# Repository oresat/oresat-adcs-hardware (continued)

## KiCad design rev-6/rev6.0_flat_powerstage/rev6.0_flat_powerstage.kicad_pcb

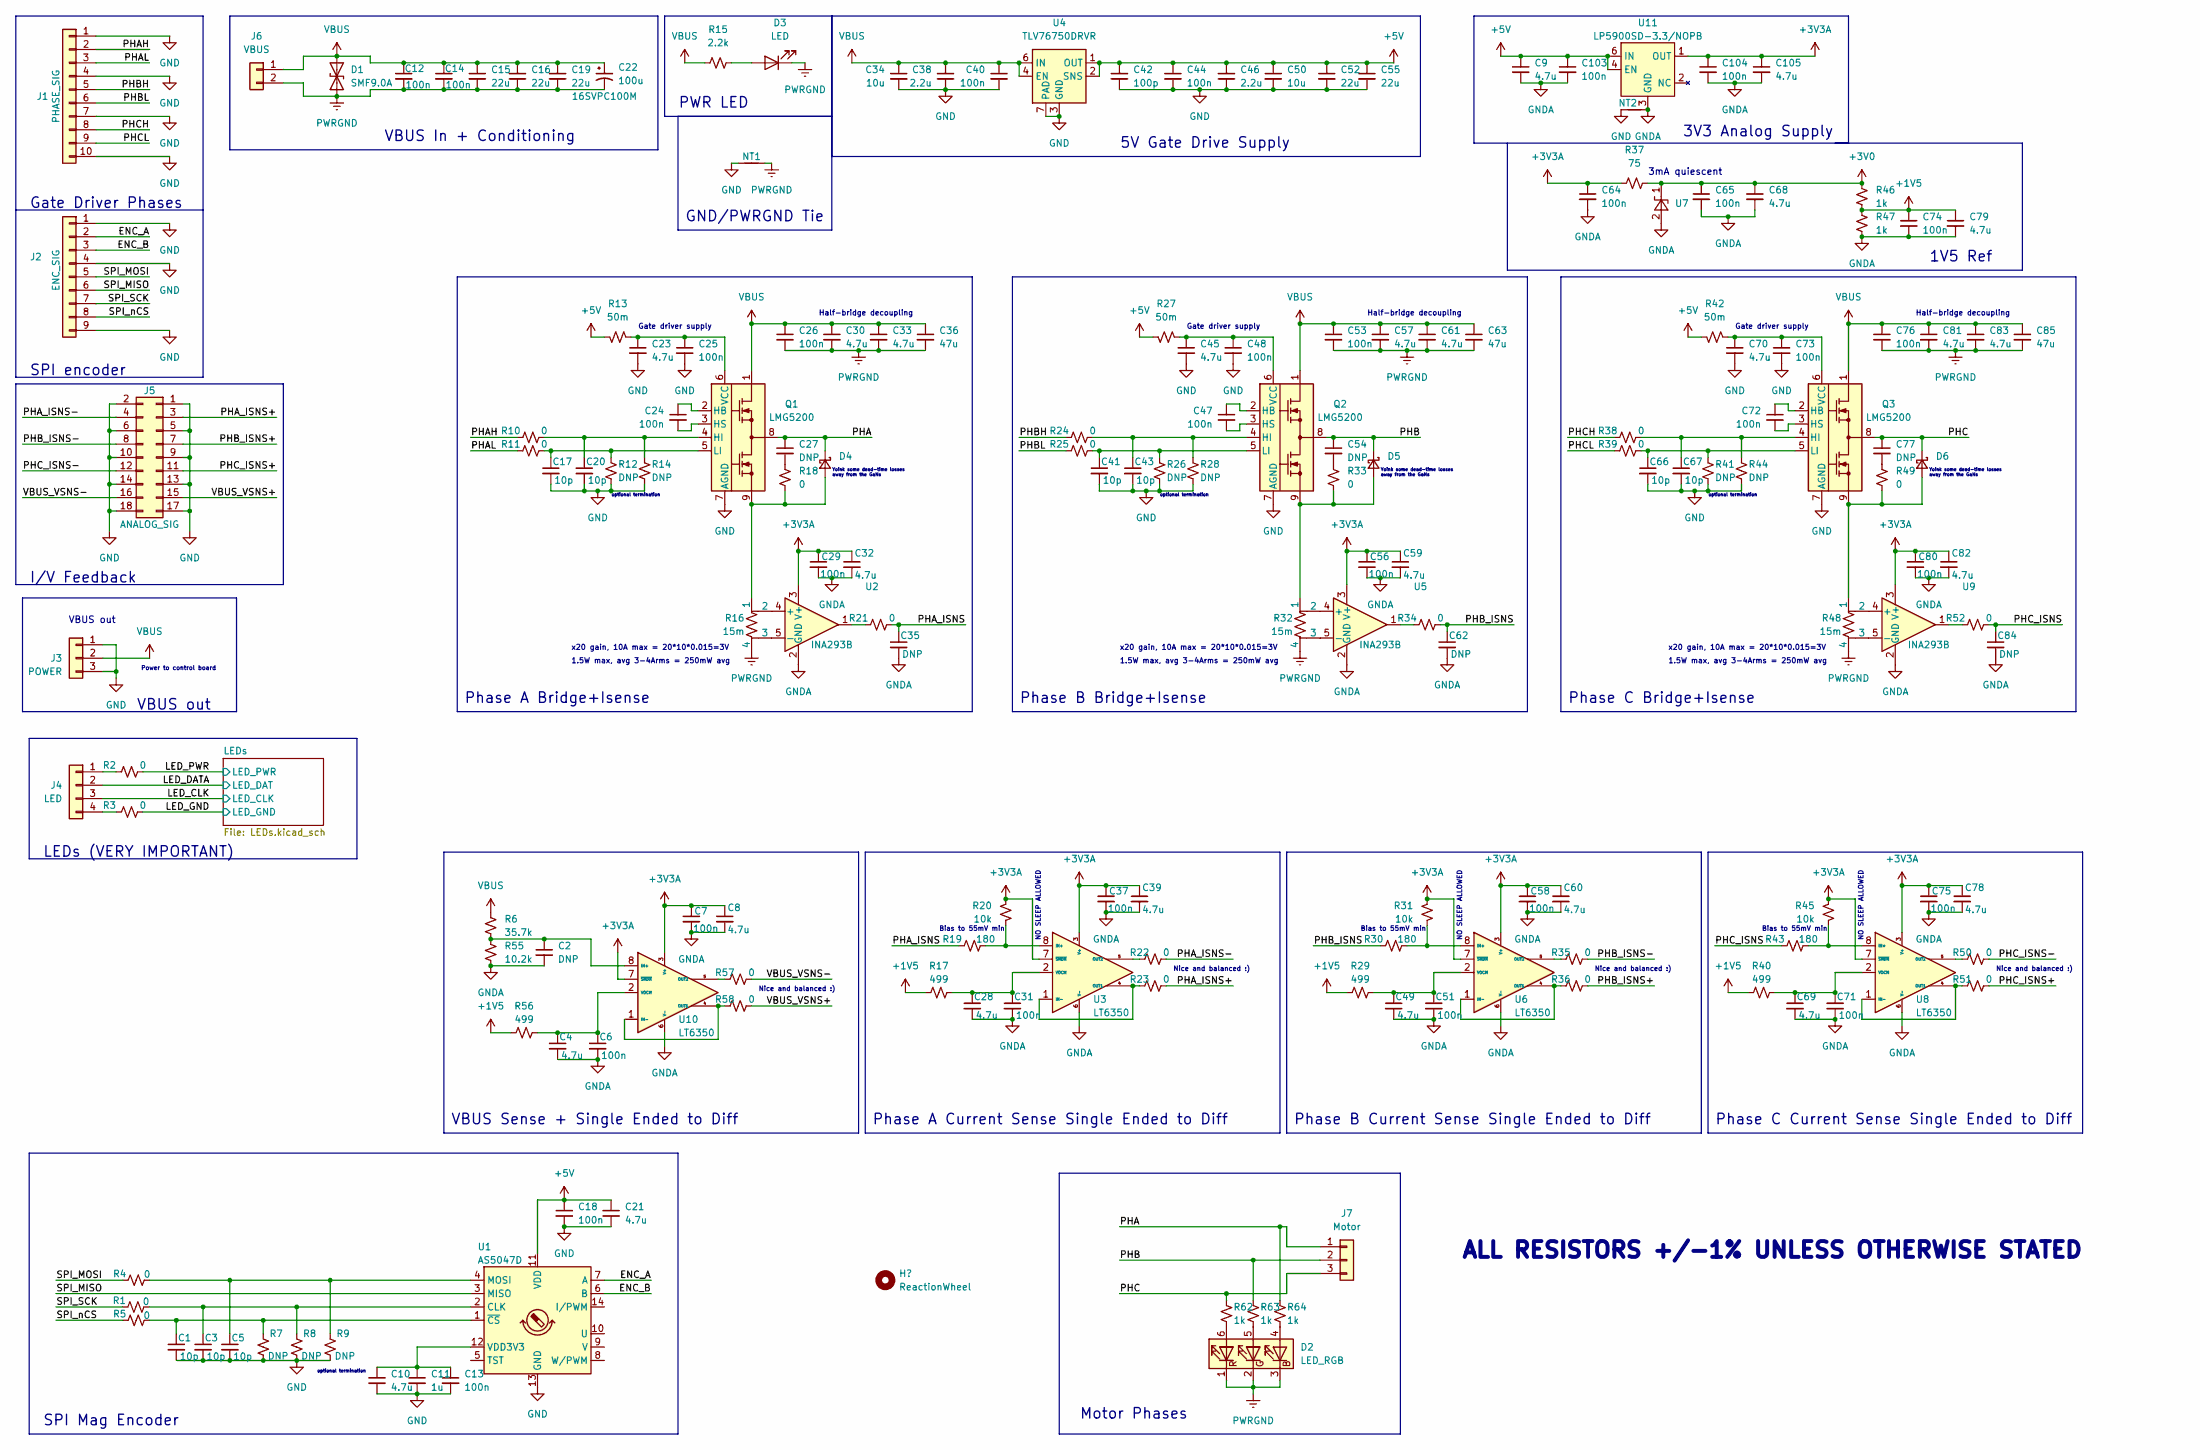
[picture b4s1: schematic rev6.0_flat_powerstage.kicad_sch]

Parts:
C1, C3, C5, C17, C20, C41, C43, C66, C67: 10p; C_0603_1608Metric
C2, C27, C35, C54, C62, C77, C84: DNP; C_0603_1608Metric
C4, C8, C9, C10, C21, C23, C28, C30, C32, C33, C39, C45, C49, C57, C59, C60, C61, C68, C69, C70, C78, C79, C81, C82, C83, C105: 4.7u; C_0603_1608Metric
C6, C7, C12, C13, C14, C18, C24, C25, C26, C29, C31, C37, C40, C44, C47, C48, C51, C53, C56, C58, C64, C65, C71, C72, C73, C74, C75, C76, C80, C103, C104: 100n; C_0603_1608Metric
C11: 1u; C_0603_1608Metric
C15, C16, C19, C52, C55: 22u; C_0805_2012Metric
C22: 100u; CP_Elec_6.3x5.9
C34: 10u; C_0805_2012Metric
C36, C63, C85: 47u; C_1210_3225Metric
C38, C46: 2.2u; C_0603_1608Metric
C42: 100p; C_0603_1608Metric
C50: 10u; C_0603_1608Metric
D1: SMF9.0A; D_SOD-123F
D2: LED_RGB; LED_RGB_PLCC-6
D3: LED; LED_0603_1608Metric
D4, D5, D6: D_Schottky_Small; D_PowerDI-123
J1: PHASE_SIG; PinSocket_1x10_P2.54mm_Horizontal
J2: ENC_SIG; PinSocket_1x09_P2.54mm_Horizontal
J3: POWER; PinSocket_1x03_P2.54mm_Horizontal
J4: LED; PinSocket_1x04_P2.54mm_Horizontal
J5: ANALOG_SIG; PinSocket_2x09_P2.54mm_Horizontal
J6: VBUS; PinSocket_1x02_P2.54mm_Vertical
J7: Motor; PinSocket_1x03_P2.54mm_Vertical
NT1: NetTie_2; NetTie-2_SMD_Pad2.0mm
NT2: NetTie_2; NetTie-2_SMD_Pad0.5mm
Q1, Q2, Q3: LMG5200; Texas_MOF0009A
R1, R2, R3, R4, R5, R10, R11, R18, R21, R22, R23, R24, R25, R33, R34, R35, R36, R38, R39, R49, R50, R51, R52, R57, R58: 0; R_0603_1608Metric
R6: 35.7k; R_0603_1608Metric
R7, R8, R9, R12, R14, R26, R28, R41, R44: DNP; R_0603_1608Metric
R13, R27, R42: 50m; R_0805_2012Metric
R15: 2.2k; R_0603_1608Metric
R16, R32, R48: 15m; KRL3216
R17, R29, R40, R56: 499; R_0603_1608Metric
R19, R30, R43: 180; R_0603_1608Metric
R20, R31, R45: 10k; R_0603_1608Metric
R37: 75; R_0603_1608Metric
R46, R47, R62, R63, R64: 1k; R_0603_1608Metric
R55: 10.2k; R_0603_1608Metric
U1: AS5047D; TSSOP-14_4.4x5mm_P0.65mm
U2, U5, U9: INA293B; SOT-23-5
U3, U6, U8, U10: LT6350; DFN-8-1EP_3x3mm_P0.5mm_EP1.65x2.38mm
U4: TLV76750DRVR; WSON-6-1EP_2x2mm_P0.65mm_EP1x1.6mm
U7: LM4040C30FTA; SOT-23
U11: LP5900SD-3.3/NOPB; TI-WSON-6-2.2x2.5

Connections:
+1V5: C74.1, C79.1, R17.1, R29.1, R40.1, R46.1, R47.2, R56.1
+3V0: C65.1, C68.1, R37.2, R46.2, U7.1 (K)
+3V3A: C7.1, C8.1, C29.1, C32.1, C37.1, C39.1, C56.1, C58.1, C59.1, C60.1, C64.1, C75.1, C78.1, C80.1, C82.1, C104.1, C105.1, R20.2, R31.2, R37.1, R45.2, U2.3 (V+), U3.3 (V+), U3.7 (~SHDN), U5.3 (V+), U6.3 (V+), U6.7 (~SHDN), U8.3 (V+), U8.7 (~SHDN), U9.3 (V+), U10.3 (V+), U10.7 (~SHDN), U11.1 (OUT)
+5V: C9.1, C18.1, C21.1, C42.1, C44.1, C46.1, C50.1, C52.1, C55.1, C103.1, R13.2, R27.2, R42.2, U1.11 (VDD), U4.1 (OUT), U4.2 (SNS), U11.4 (EN), U11.6 (IN)
/ENC_A: J2.2, U1.7 (A)
/ENC_B: J2.3, U1.6 (B)
/LED_CLK: J4.3; also elsewhere on the board
/LED_DATA: J4.2; also elsewhere on the board
/LED_GND: R3.2; also elsewhere on the board
/LED_PWR: R2.2; also elsewhere on the board
/PHA: C27.1, D4.1 (K), J7.1, Q1.8, R64.1
/PHAH: J1.2, R10.1
/PHAL: J1.3, R11.1
/PHA_ISNS: C35.1, R19.1, R21.2
/PHA_ISNS+: J5.3, R23.2
/PHA_ISNS-: J5.4, R22.2
/PHB: C54.1, D5.1 (K), J7.2, Q2.8, R63.1
/PHBH: J1.5, R24.1
/PHBL: J1.6, R25.1
/PHB_ISNS: C62.1, R30.1, R34.2
/PHB_ISNS+: J5.7, R36.2
/PHB_ISNS-: J5.8, R35.2
/PHC: C77.1, D6.1 (K), J7.3, Q3.8, R62.1
/PHCH: J1.8, R38.1
/PHCL: J1.9, R39.1
/PHC_ISNS: C84.1, R43.1, R52.2
/PHC_ISNS+: J5.11, R51.2
/PHC_ISNS-: J5.12, R50.2
/SPI_MISO: J2.6, U1.3 (MISO)
/SPI_MOSI: J2.5, R4.1
/SPI_SCK: J2.7, R1.1
/SPI_nCS: J2.8, R5.1
/VBUS_VSNS+: J5.15, R58.2
/VBUS_VSNS-: J5.16, R57.2
GND: C1.2, C3.2, C5.2, C10.2, C11.2, C13.2, C17.2, C18.2, C20.2, C21.2, C23.2, C25.2, C34.2, C38.2, C40.2, C41.2, C42.2, C43.2, C44.2, C45.2, C46.2, C48.2, C50.2, C52.2, C55.2, C66.2, C67.2, C70.2, C73.2, J1.1, J1.4, J1.7, J1.10, J2.1, J2.4, J2.9, J3.1, J3.3, J5.1, J5.2, J5.5, J5.6, J5.9, J5.10, J5.13, J5.14, J5.17, J5.18, NT1.1, NT2.1, Q1.7 (AGND), Q2.7 (AGND), Q3.7 (AGND), R7.2, R8.2, R9.2, R12.2, R14.2, R26.2, R28.2, R41.2, R44.2, U1.13 (GND), U4.3 (GND), U4.5 (GND), U4.7 (PAD); also elsewhere on the board
GNDA: C2.2, C4.2, C6.2, C7.2, C8.2, C9.2, C28.2, C29.2, C31.2, C32.2, C35.2, C37.2, C39.2, C49.2, C51.2, C56.2, C58.2, C59.2, C60.2, C62.2, C64.2, C65.2, C68.2, C69.2, C71.2, C74.2, C75.2, C78.2, C79.2, C80.2, C82.2, C84.2, C103.2, C104.2, C105.2, NT2.2, R47.1, R55.2, U2.2 (GND), U3.6 (V-), U3.9 (EP), U5.2 (GND), U6.6 (V-), U6.9 (EP), U7.2 (A), U8.6 (V-), U8.9 (EP), U9.2 (GND), U10.6 (V-), U10.9 (EP), U11.3 (GND), U11.7 (EP)
unnamed: C1.1, R5.2, R7.1, U1.1 (~CS)
unnamed: C2.1, R6.2, R55.1, U10.8 (IN+)
unnamed: C3.1, R1.2, R8.1, U1.2 (CLK)
unnamed: C4.1, C6.1, R56.2, U10.2 (VOCM)
unnamed: C5.1, R4.2, R9.1, U1.4 (MOSI)
unnamed: C10.1, C11.1, C13.1, U1.12 (VDD3V3)
unnamed: C17.1, Q1.5 (LI), R11.2, R12.1
unnamed: C20.1, Q1.4 (HI), R10.2, R14.1
unnamed: C23.1, C25.1, Q1.6 (VCC), R13.1
unnamed: C24.1, Q1.2 (HB)
unnamed: C24.2, Q1.3 (HS)
unnamed: C27.2, R18.1
unnamed: C28.1, C31.1, R17.2, U3.2 (VOCM)
unnamed: C41.1, Q2.5 (LI), R25.2, R26.1
unnamed: C43.1, Q2.4 (HI), R24.2, R28.1
unnamed: C45.1, C48.1, Q2.6 (VCC), R27.1
unnamed: C47.1, Q2.2 (HB)
unnamed: C47.2, Q2.3 (HS)
unnamed: C49.1, C51.1, R29.2, U6.2 (VOCM)
unnamed: C54.2, R33.1
unnamed: C66.1, Q3.5 (LI), R39.2, R41.1
unnamed: C67.1, Q3.4 (HI), R38.2, R44.1
unnamed: C69.1, C71.1, R40.2, U8.2 (VOCM)
unnamed: C70.1, C73.1, Q3.6 (VCC), R42.1
unnamed: C72.1, Q3.2 (HB)
unnamed: C72.2, Q3.3 (HS)
unnamed: C77.2, R49.1
unnamed: D2.4 (BA), R64.2
unnamed: D2.5 (GA), R63.2
unnamed: D2.6 (RA), R62.2
unnamed: D3.2 (A), R15.2
unnamed: D4.2 (A), Q1.9, R16.1, R18.2
unnamed: D5.2 (A), Q2.9, R32.1, R33.2
unnamed: D6.2 (A), Q3.9, R48.1, R49.2
unnamed: J4.1, R2.1
unnamed: J4.4, R3.1
unnamed: R16.2, U2.4 (+)
unnamed: R16.3, U2.5 (-)
unnamed: R19.2, R20.1, U3.8 (IN+)
unnamed: R21.1, U2.1
unnamed: R22.1, U3.5 (OUT2)
unnamed: R23.1, U3.1 (IN-), U3.4 (OUT1)
unnamed: R30.2, R31.1, U6.8 (IN+)
unnamed: R32.2, U5.4 (+)
unnamed: R32.3, U5.5 (-)
unnamed: R34.1, U5.1
unnamed: R35.1, U6.5 (OUT2)
unnamed: R36.1, U6.1 (IN-), U6.4 (OUT1)
unnamed: R43.2, R45.1, U8.8 (IN+)
unnamed: R48.2, U9.4 (+)
unnamed: R48.3, U9.5 (-)
unnamed: R50.1, U8.5 (OUT2)
unnamed: R51.1, U8.1 (IN-), U8.4 (OUT1)
unnamed: R52.1, U9.1
unnamed: R57.1, U10.5 (OUT2)
unnamed: R58.1, U10.1 (IN-), U10.4 (OUT1)
PWRGND: C12.2, C14.2, C15.2, C16.2, C19.2, C22.2, C26.2, C30.2, C33.2, C36.2, C53.2, C57.2, C61.2, C63.2, C76.2, C81.2, C83.2, C85.2, D1.1 (A1), D2.1 (RK), D2.2 (GK), D2.3 (BK), D3.1 (K), J6.2, NT1.2, R16.4, R32.4, R48.4
VBUS: C12.1, C14.1, C15.1, C16.1, C19.1, C22.1, C26.1, C30.1, C33.1, C34.1, C36.1, C38.1, C40.1, C53.1, C57.1, C61.1, C63.1, C76.1, C81.1, C83.1, C85.1, D1.2 (A2), J3.2, J6.1, Q1.1, Q2.1, Q3.1, R6.1, R15.1, U4.4 (EN), U4.6 (IN)

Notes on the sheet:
Phase A Bridge+Isense
Yoink some dead-time losses away from the GaNs
Nice and balanced :)
optional termination
Half-bridge decoupling
3mA quiescent
Power to control board
x20 gain, 10A max = 20*10*0.015=3V
VBUS out
SPI Mag Encoder
Gate Driver Phases
I/V Feedback
3V3 Analog Supply
LEDs (VERY IMPORTANT)
1.5W max, avg 3-4Arms = 250mW avg
SPI encoder
GND/PWRGND Tie
ALL RESISTORS +/-1% UNLESS OTHERWISE STATED
1V5 Ref
NO SLEEP ALLOWED
Phase C Current Sense Single Ended to Diff
Motor Phases
Bias to 55mV min
Gate driver supply
VBUS In + Conditioning
Phase A Current Sense Single Ended to Diff
5V Gate Drive Supply
Phase B Bridge+Isense
Phase C Bridge+Isense
PWR LED
Phase B Current Sense Single Ended to Diff
VBUS Sense + Single Ended to Diff

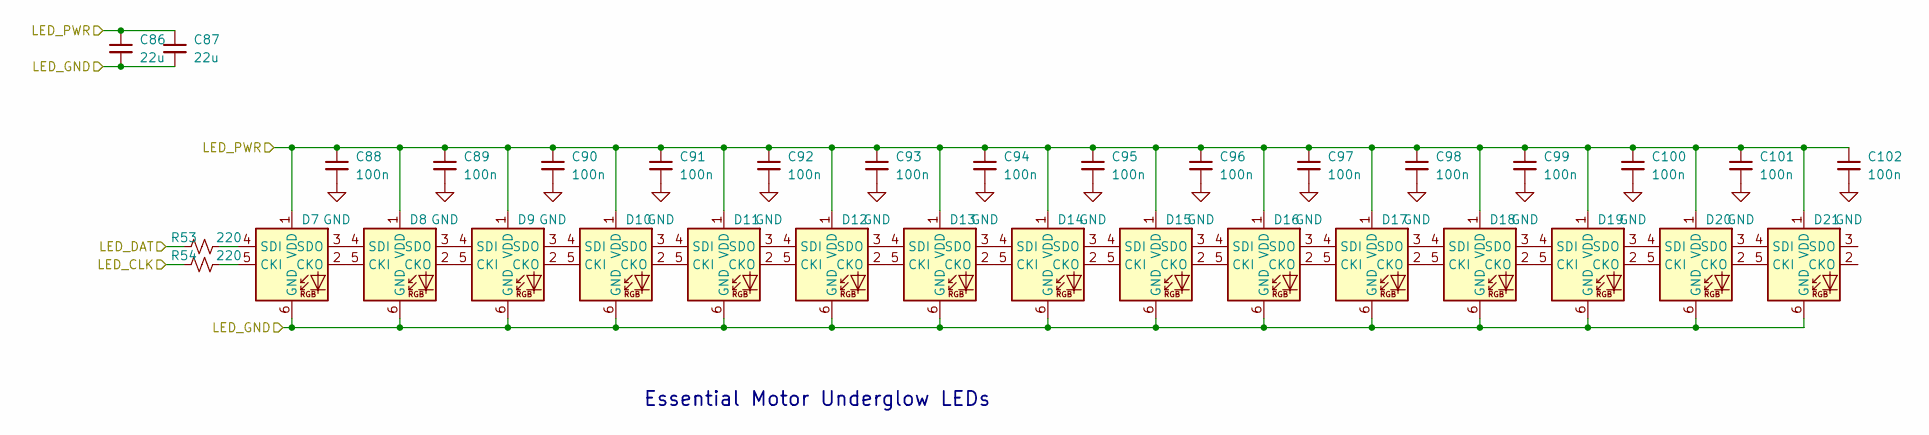
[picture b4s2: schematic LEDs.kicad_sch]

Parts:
C86, C87: 22u; C_0805_2012Metric
C88, C89, C90, C91, C92, C93, C94, C95, C96, C97, C98, C99, C100, C101, C102: 100n; C_0603_1608Metric
D7, D8, D9, D10, D11, D12, D13, D14, D15, D16, D17, D18, D19, D20, D21: APA102-2020; LED-APA102-2020
R53, R54: 220; R_0603_1608Metric

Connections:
/LED_CLK: R54.1; also elsewhere on the board
/LED_DATA: R53.1; also elsewhere on the board
/LED_GND: C86.2, C87.2, D7.6 (GND), D8.6 (GND), D9.6 (GND), D10.6 (GND), D11.6 (GND), D12.6 (GND), D13.6 (GND), D14.6 (GND), D15.6 (GND), D16.6 (GND), D17.6 (GND), D18.6 (GND), D19.6 (GND), D20.6 (GND), D21.6 (GND); also elsewhere on the board
/LED_PWR: C86.1, C87.1, C88.1, C89.1, C90.1, C91.1, C92.1, C93.1, C94.1, C95.1, C96.1, C97.1, C98.1, C99.1, C100.1, C101.1, C102.1, D7.1 (VDD), D8.1 (VDD), D9.1 (VDD), D10.1 (VDD), D11.1 (VDD), D12.1 (VDD), D13.1 (VDD), D14.1 (VDD), D15.1 (VDD), D16.1 (VDD), D17.1 (VDD), D18.1 (VDD), D19.1 (VDD), D20.1 (VDD), D21.1 (VDD); also elsewhere on the board
GND: C88.2, C89.2, C90.2, C91.2, C92.2, C93.2, C94.2, C95.2, C96.2, C97.2, C98.2, C99.2, C100.2, C101.2, C102.2; also elsewhere on the board
unnamed: D7.2 (CKO), D8.5 (CKI)
unnamed: D7.3 (SDO), D8.4 (SDI)
unnamed: D7.4 (SDI), R53.2
unnamed: D7.5 (CKI), R54.2
unnamed: D8.2 (CKO), D9.5 (CKI)
unnamed: D8.3 (SDO), D9.4 (SDI)
unnamed: D10.2 (CKO), D11.5 (CKI)
unnamed: D10.3 (SDO), D11.4 (SDI)
unnamed: D9.3 (SDO), D10.4 (SDI)
unnamed: D9.2 (CKO), D10.5 (CKI)
unnamed: D11.2 (CKO), D12.5 (CKI)
unnamed: D11.3 (SDO), D12.4 (SDI)
unnamed: D12.2 (CKO), D13.5 (CKI)
unnamed: D12.3 (SDO), D13.4 (SDI)
unnamed: D13.2 (CKO), D14.5 (CKI)
unnamed: D13.3 (SDO), D14.4 (SDI)
unnamed: D14.2 (CKO), D15.5 (CKI)
unnamed: D14.3 (SDO), D15.4 (SDI)
unnamed: D15.2 (CKO), D16.5 (CKI)
unnamed: D15.3 (SDO), D16.4 (SDI)
unnamed: D16.2 (CKO), D17.5 (CKI)
unnamed: D16.3 (SDO), D17.4 (SDI)
unnamed: D17.2 (CKO), D18.5 (CKI)
unnamed: D17.3 (SDO), D18.4 (SDI)
unnamed: D18.2 (CKO), D19.5 (CKI)
unnamed: D18.3 (SDO), D19.4 (SDI)
unnamed: D19.2 (CKO), D20.5 (CKI)
unnamed: D19.3 (SDO), D20.4 (SDI)
unnamed: D20.2 (CKO), D21.5 (CKI)
unnamed: D20.3 (SDO), D21.4 (SDI)

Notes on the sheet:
Essential Motor Underglow LEDs

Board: 2 copper layers, 210 parts (0 on the bottom side), 124 nets, no tracks yet.

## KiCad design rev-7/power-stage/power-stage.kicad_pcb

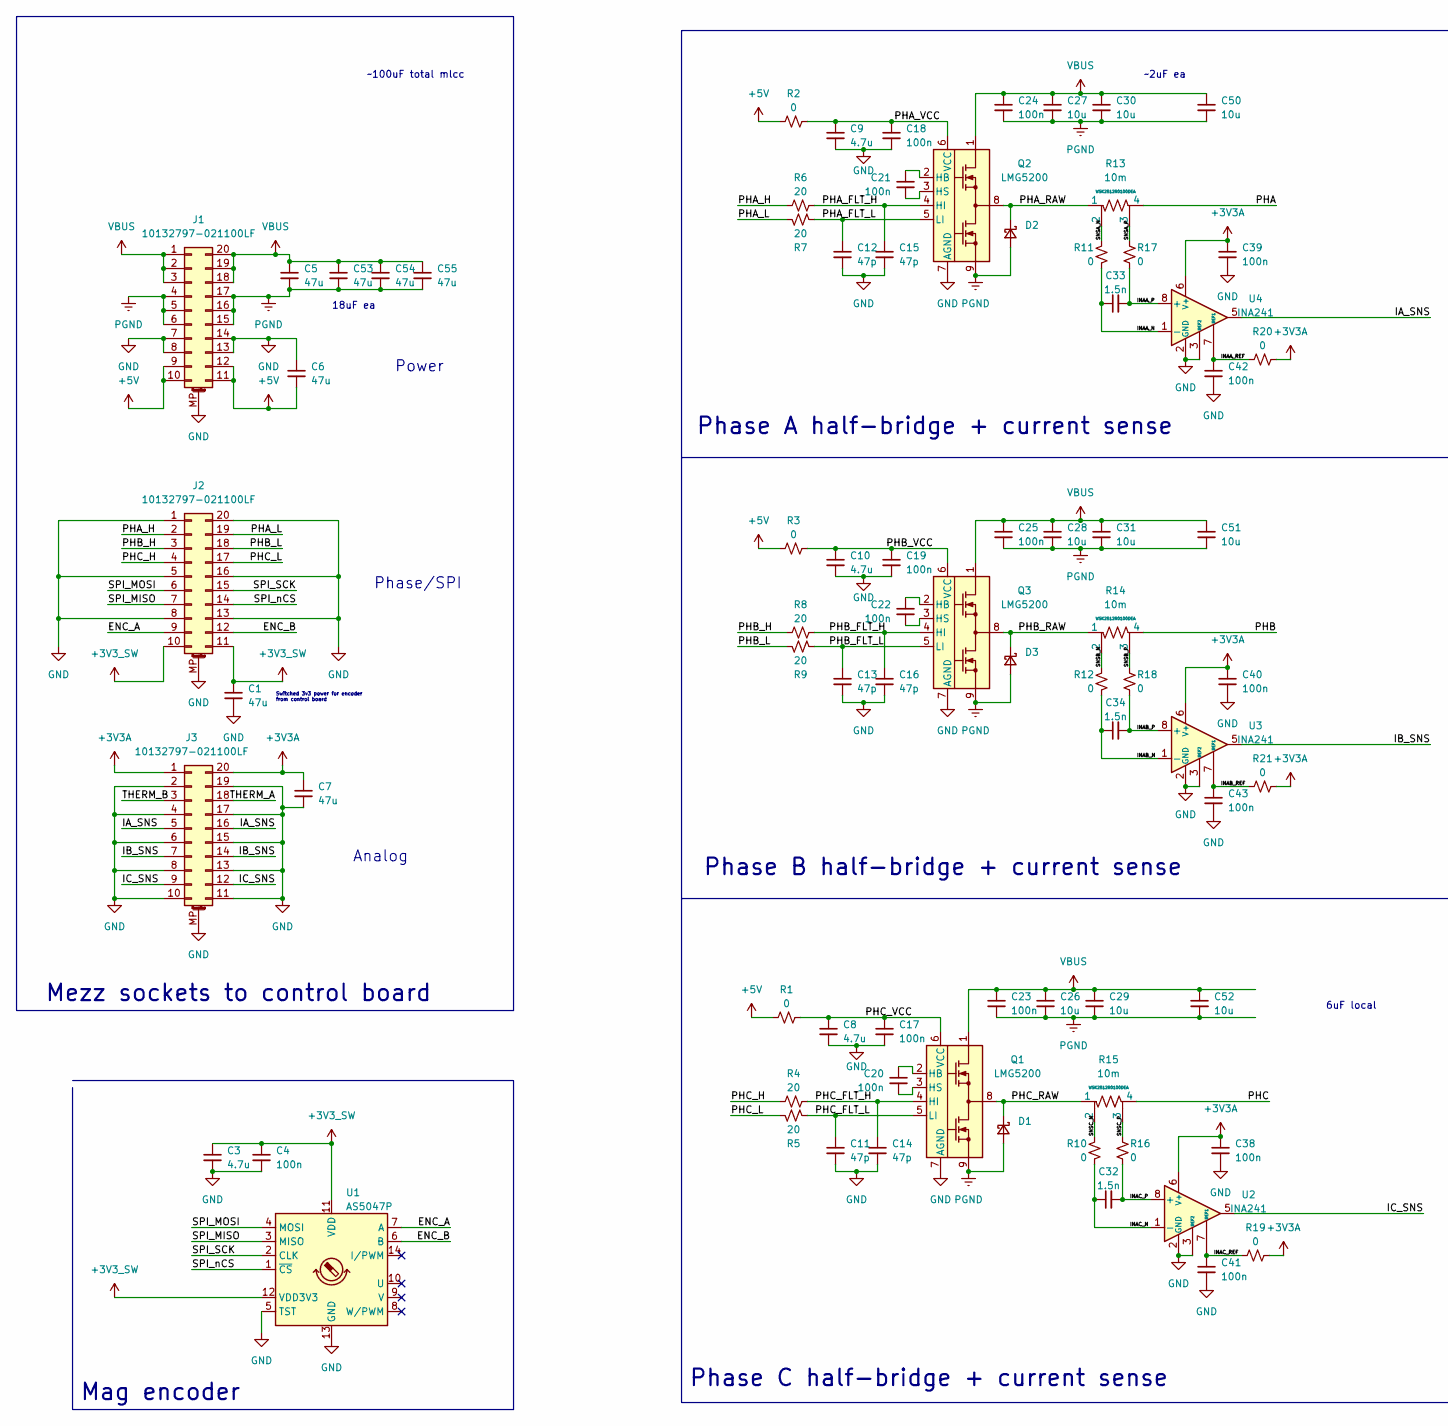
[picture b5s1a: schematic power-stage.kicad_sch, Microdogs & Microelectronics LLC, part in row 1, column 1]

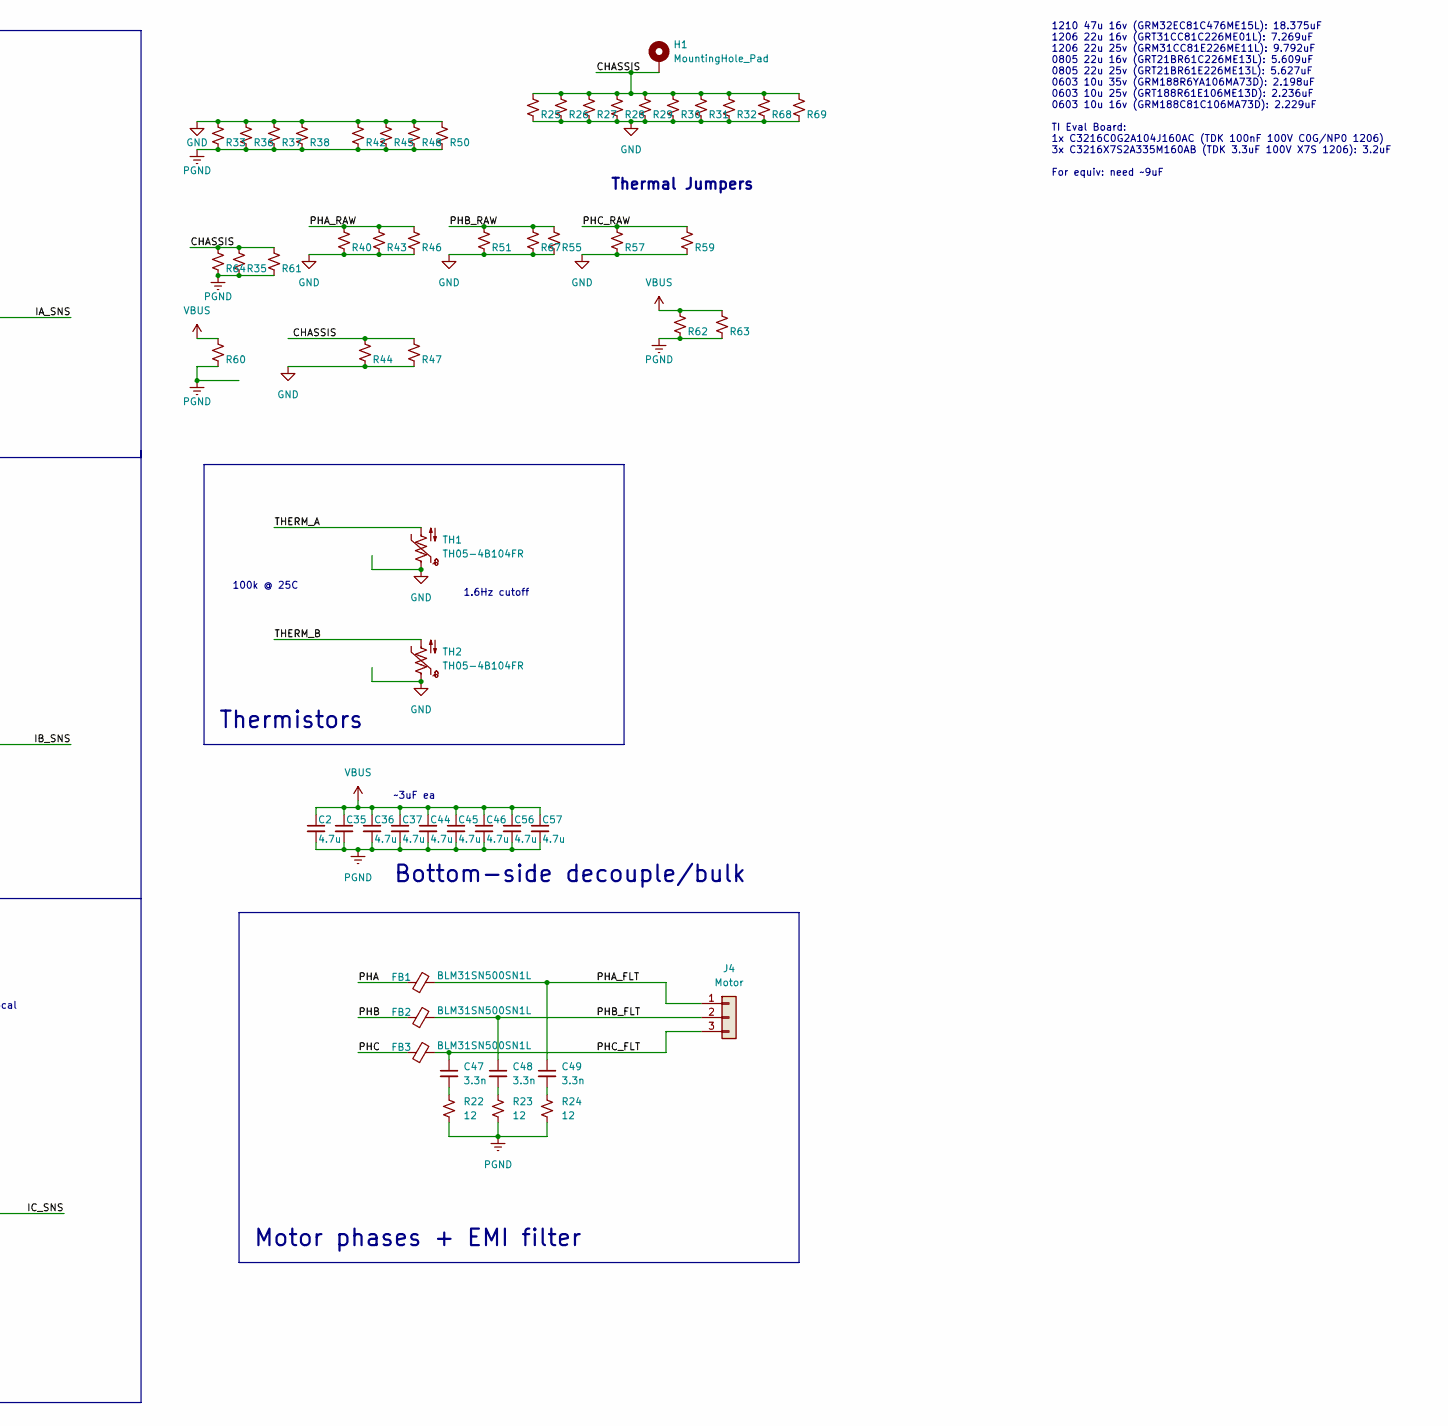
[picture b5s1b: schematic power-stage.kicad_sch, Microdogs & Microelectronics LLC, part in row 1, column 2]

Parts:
C1, C5, C6, C7, C53, C54, C55: 47u; C_1210_3225Metric
C2, C35, C36, C37, C44, C45, C46, C56, C57: 4.7u; C_0805_2012Metric; MPN GCM21BC7YA475KE36L
C3, C8, C9, C10: 4.7u; C_0603_1608Metric
C4, C17, C18, C19, C20, C21, C22, C38, C39, C40, C41, C42, C43: 100n; C_0402_1005Metric
C11, C12, C13, C14, C15, C16: 47p; C_0402_1005Metric
C23, C24, C25: 100n; C_0603_1608Metric
C26, C27, C28, C29, C30, C31, C50, C51, C52: 10u; C_0603_1608Metric
C32, C33, C34: 1.5n; C_0402_1005Metric
C47, C48, C49: 3.3n; C_0805_2012Metric
D1, D2, D3: D_Schottky_Small; D_PowerDI-123
FB1, FB2, FB3: BLM31SN500SN1L; L_1206_3216Metric
H1: MountingHole_Pad; board-def-rev7.2
J1, J2, J3: 10132797-021100LF
J4: Motor; SolderWire-0.5sqmm_1x03_P4.6mm_D0.9mm_OD2.1mm
Q1, Q2, Q3: LMG5200; Texas_MOF0009A
R1, R2, R3: 0; R_0603_1608Metric
R4, R5, R6, R7, R8, R9: 20; R_0402_1005Metric
R10, R11, R12, R16, R17, R18, R19, R20, R21: 0; R_0402_1005Metric
R13, R14, R15: 10m; R_Shunt_Vishay_WSK2512_6332Metric_T1.19mm
R22, R23, R24: 12; R_0805_2012Metric
R25, R26, R27, R28, R29, R30, R31, R32, R33, R36, R37, R38, R40, R42, R43, R45, R46, R48, R50, R51, R55, R57, R59, R60, R62, R63, R64, R67, R68, R69: THJP0603ABT1; R_0603_1608Metric
R35, R44, R47, R61: THJP1206ABT1; R_1206_3216Metric
TH1, TH2: TH05-4B104FR; R_0402_1005Metric
U1: AS5047P; TSSOP-14_4.4x5mm_P0.65mm
U2, U3, U4: INA241; SOT-23-8

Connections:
+3V3A: C7.1, C38.1, C39.1, C40.1, J3.1, J3.20, R19.2, R20.2, R21.2, U2.6 (V+), U3.6 (V+), U4.6 (V+)
+3V3_SW: C1.1, C3.1, C4.1, J2.10, J2.11, U1.11 (VDD), U1.12 (VDD3V3)
+5V: C6.2, J1.9, J1.10, J1.11, J1.12, R1.1, R2.1, R3.1
/CHASSIS: H1.1, R25.1, R26.1, R27.1, R28.1, R29.1, R30.1, R31.1, R32.1, R35.1, R44.1, R47.1, R61.1, R64.1, R68.1, R69.1
/ENC_A: J2.9, U1.7 (A)
/ENC_B: J2.12, U1.6 (B)
/IA_SNS: J3.5, J3.16, U4.5
/IB_SNS: J3.7, J3.14, U3.5
/IC_SNS: J3.9, J3.12, U2.5
/INAA_N: C33.1, R11.1, U4.1 (-)
/INAA_P: C33.2, R17.2, U4.8 (+)
/INAA_REF: C42.1, R20.1, U4.7 (REF1)
/INAB_N: C34.1, R12.1, U3.1 (-)
/INAB_P: C34.2, R18.2, U3.8 (+)
/INAB_REF: C43.1, R21.1, U3.7 (REF1)
/INAC_N: C32.1, R10.1, U2.1 (-)
/INAC_P: C32.2, R16.2, U2.8 (+)
/INAC_REF: C41.1, R19.1, U2.7 (REF1)
/PHA: FB1.1, R13.4
/PHA_FLT: C49.1, FB1.2, J4.1
/PHA_FLT_H: C15.1, Q2.4 (HI), R6.2
/PHA_FLT_L: C12.1, Q2.5 (LI), R7.2
/PHA_H: J2.2, R6.1
/PHA_L: J2.19, R7.1
/PHA_RAW: D2.1 (K), Q2.8, R13.1, R40.1, R43.1, R46.1
/PHA_VCC: C9.1, C18.1, Q2.6 (VCC), R2.2
/PHB: FB2.1, R14.4
/PHB_FLT: C48.1, FB2.2, J4.2
/PHB_FLT_H: C16.1, Q3.4 (HI), R8.2
/PHB_FLT_L: C13.1, Q3.5 (LI), R9.2
/PHB_H: J2.3, R8.1
/PHB_L: J2.18, R9.1
/PHB_RAW: D3.1 (K), Q3.8, R14.1, R51.1, R55.1, R67.1
/PHB_VCC: C10.1, C19.1, Q3.6 (VCC), R3.2
/PHC: FB3.1, R15.4
/PHC_FLT: C47.1, FB3.2, J4.3
/PHC_FLT_H: C14.1, Q1.4 (HI), R4.2
/PHC_FLT_L: C11.1, Q1.5 (LI), R5.2
/PHC_H: J2.4, R4.1
/PHC_L: J2.17, R5.1
/PHC_RAW: D1.1 (K), Q1.8, R15.1, R57.1, R59.1
/PHC_VCC: C8.1, C17.1, Q1.6 (VCC), R1.2
/SNSA_N: R11.2, R13.2
/SNSA_P: R13.3, R17.1
/SNSB_N: R12.2, R14.2
/SNSB_P: R14.3, R18.1
/SNSC_N: R10.2, R15.2
/SNSC_P: R15.3, R16.1
/SPI_MISO: J2.7, U1.3 (MISO)
/SPI_MOSI: J2.6, U1.4 (MOSI)
/SPI_SCK: J2.15, U1.2 (CLK)
/SPI_nCS: J2.14, U1.1 (~CS)
/THERM_A: J3.18, TH1.2
/THERM_B: J3.3, TH2.2
GND: C1.2, C3.2, C4.2, C6.1, C7.2, C8.2, C9.2, C10.2, C11.2, C12.2, C13.2, C14.2, C15.2, C16.2, C17.2, C18.2, C19.2, C38.2, C39.2, C40.2, C41.2, C42.2, C43.2, J1.7, J1.8, J1.13, J1.14, J1.MP (MountPin), J2.1, J2.5, J2.8, J2.13, J2.16, J2.20, J2.MP (MountPin), J3.2, J3.4, J3.6, J3.8, J3.10, J3.11, J3.13, J3.15, J3.17, J3.19, J3.MP (MountPin), Q1.7 (AGND), Q2.7 (AGND), Q3.7 (AGND), R25.2, R26.2, R27.2, R28.2, R29.2, R30.2, R31.2, R32.2, R33.1, R36.1, R37.1, R38.1, R40.2, R42.1, R43.2, R44.2, R45.1, R46.2, R47.2, R48.1, R50.1, R51.2, R55.2, R57.2, R59.2, R67.2, R68.2, R69.2, TH1.1, TH2.1, U1.5 (TST), U1.13 (GND), U2.2 (GND), U2.3 (REF2), U2.4 (GND), U3.2 (GND), U3.3 (REF2), U3.4 (GND), U4.2 (GND), U4.3 (REF2), U4.4 (GND)
unnamed: C47.2, R22.1
unnamed: C48.2, R23.1
unnamed: C49.2, R24.1
unnamed: C20.1, Q1.2 (HB)
unnamed: C20.2, Q1.3 (HS)
unnamed: C21.1, Q2.2 (HB)
unnamed: C21.2, Q2.3 (HS)
unnamed: C22.1, Q3.2 (HB)
unnamed: C22.2, Q3.3 (HS)
PGND: C2.2, C5.2, C23.2, C24.2, C25.2, C26.2, C27.2, C28.2, C29.2, C30.2, C31.2, C35.2, C36.2, C37.2, C44.2, C45.2, C46.2, C50.2, C51.2, C52.2, C53.2, C54.2, C55.2, C56.2, C57.2, D1.2 (A), D2.2 (A), D3.2 (A), J1.4, J1.5, J1.6, J1.15, J1.16, J1.17, Q1.9, Q2.9, Q3.9, R22.2, R23.2, R24.2, R33.2, R35.2, R36.2, R37.2, R38.2, R42.2, R45.2, R48.2, R50.2, R60.2, R61.2, R62.2, R63.2, R64.2
VBUS: C2.1, C5.1, C23.1, C24.1, C25.1, C26.1, C27.1, C28.1, C29.1, C30.1, C31.1, C35.1, C36.1, C37.1, C44.1, C45.1, C46.1, C50.1, C51.1, C52.1, C53.1, C54.1, C55.1, C56.1, C57.1, J1.1, J1.2, J1.3, J1.18, J1.19, J1.20, Q1.1, Q2.1, Q3.1, R60.1, R62.1, R63.1

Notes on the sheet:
~2uF ea
Analog
Thermal Jumpers
Motor phases + EMI filter
6uF local
Power
Phase/SPI
100k @ 25C
Thermistors
1210 47u 16v (GRM32EC81C476ME15L): 18.375uF 1206 22u 16v (GRT31CC81C226ME01L): 7.269uF 1206 22u 25v (GRM31CC81E226ME11L): 9.792uF 0805 22u 16v (GRT21BR61C226ME13L): 5.609uF 0805 22u 25v (GRT21BR61E226ME13L): 5.627uF 0603 10u 35v (GRM188R6YA106MA73D): 2.198uF 0603 10u 25v (GRT188R61E106ME13D): 2.236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
1.6Hz cutoff
~3uF ea
Phase A half-bridge + current sense
~100uF total mlcc
Mag encoder
Mezz sockets to control board
Phase B half-bridge + current sense
Switched 3v3 power for encoder from control board
Phase C half-bridge + current sense
18uF ea
Bottom-side decouple/bulk

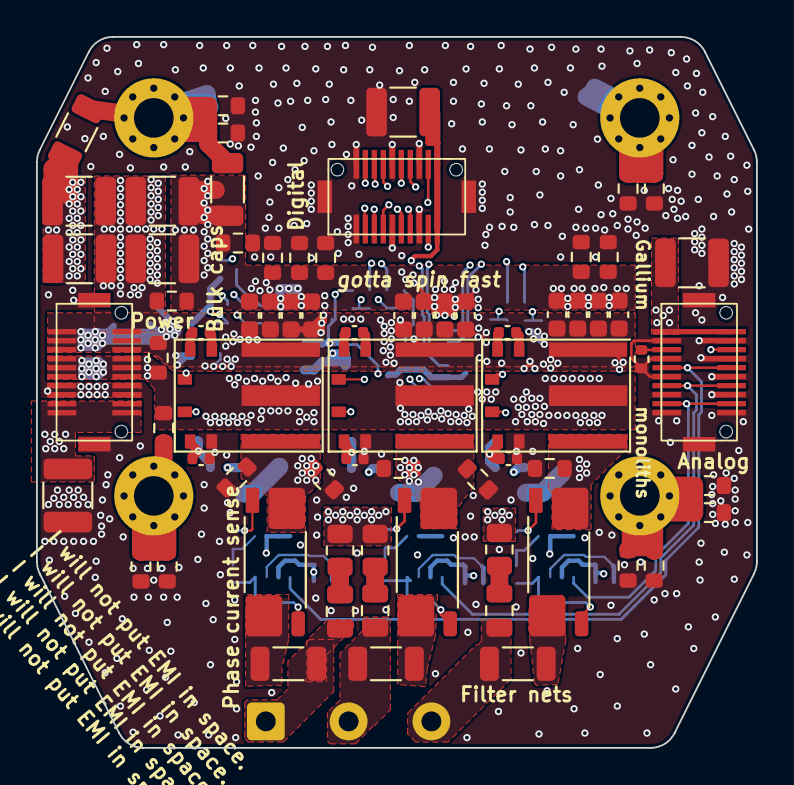
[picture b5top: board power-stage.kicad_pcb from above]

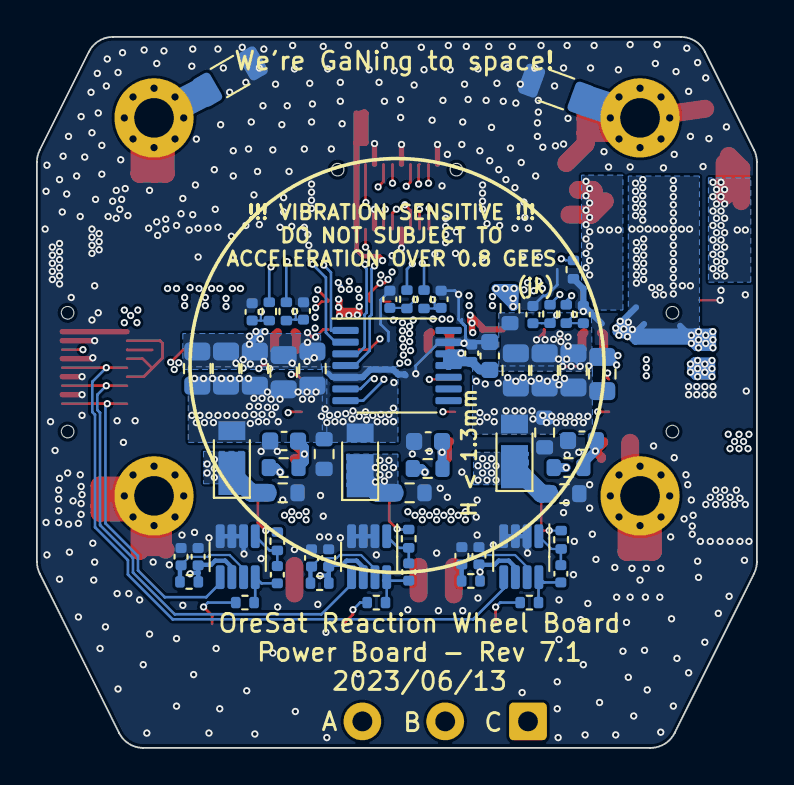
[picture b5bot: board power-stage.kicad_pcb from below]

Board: 6 copper layers, 40.0 x 39.5 mm, 135 parts (63 on the bottom side), 66 nets.
